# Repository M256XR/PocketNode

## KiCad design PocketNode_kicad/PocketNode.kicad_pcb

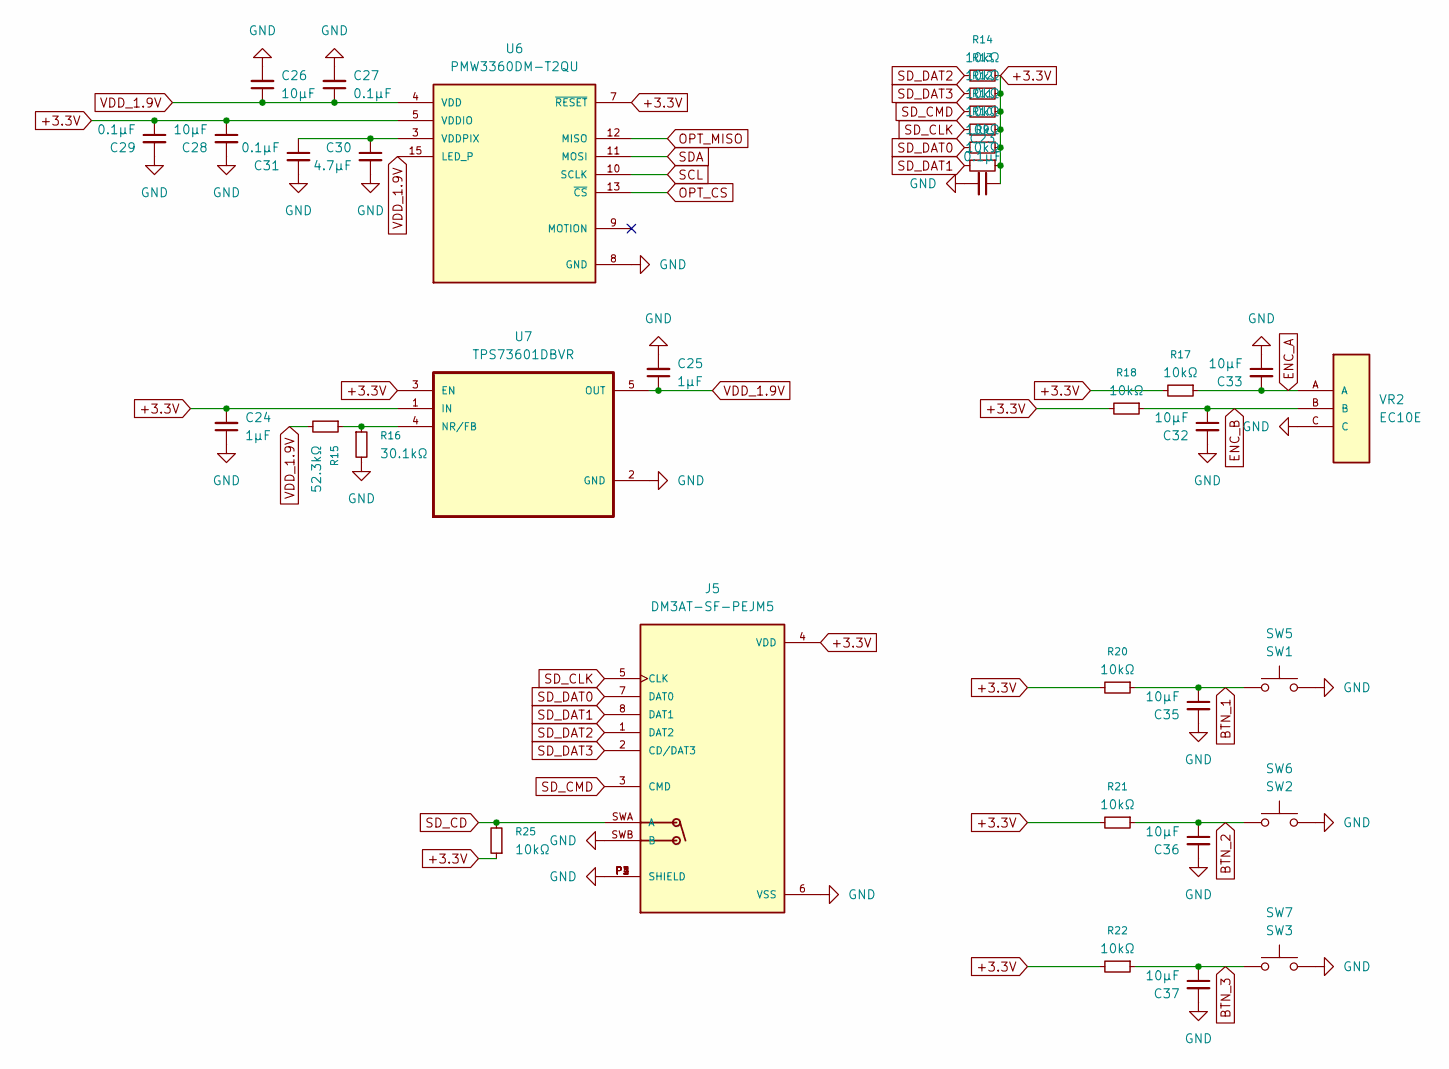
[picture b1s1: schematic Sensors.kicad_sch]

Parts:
C23, C27, C29, C31: 0.1μF; C_0603_1608Metric_Pad1.08x0.95mm_HandSolder
C24, C25: 1μF; C_0603_1608Metric_Pad1.08x0.95mm_HandSolder
C26, C28, C32, C33, C35, C36, C37: 10μF; C_0603_1608Metric_Pad1.08x0.95mm_HandSolder
C30: 4.7μF; C_0603_1608Metric_Pad1.08x0.95mm_HandSolder
J5: DM3AT-SF-PEJM5; HRS_DM3AT-SF-PEJM5
R9, R10, R11, R12, R13, R14, R17, R18, R20, R21, R22, R25: 10kΩ; R_0603_1608Metric_Pad0.98x0.95mm_HandSolder
R15: 52.3kΩ; R_0603_1608Metric_Pad0.98x0.95mm_HandSolder
R16: 30.1kΩ; R_0603_1608Metric_Pad0.98x0.95mm_HandSolder
SW5: SW1; SW_PUSH_6mm
SW6: SW2; SW_PUSH_6mm
SW7: SW3; SW_PUSH_6mm
U6: PMW3360DM-T2QU; PMW3360
U7: TPS73601DBVR; SOT95P280X145-5N
VR2: EC10E; TRIM_EC10E1220501

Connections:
+3.3V: C23.1, C24.2, C28.1, C29.1, J5.4 (VDD), R9.1, R10.1, R11.1, R12.1, R13.1, R14.1, R17.2, R18.2, R20.2, R21.2, R22.2, R25.1, U6.5 (VDDIO), U6.7 (~RESET), U7.1 (IN), U7.3 (EN); also elsewhere on the board
BTN_1: C35.1, R20.1, SW5.1; also elsewhere on the board
BTN_2: C36.1, R21.1, SW6.1; also elsewhere on the board
BTN_3: C37.1, R22.1, SW7.1; also elsewhere on the board
ENC_A: C33.2, R17.1, VR2.A; also elsewhere on the board
ENC_B: C32.1, R18.1, VR2.B; also elsewhere on the board
GND: C23.2, C24.1, C25.2, C26.2, C27.2, C28.2, C29.2, C30.2, C31.2, C32.2, C33.1, C35.2, C36.2, C37.2, J5.6 (VSS), J5.P1 (SHIELD), J5.P2 (SHIELD), J5.P3 (SHIELD), J5.P4 (SHIELD), J5.SWB (B), R16.2, SW5.2, SW6.2, SW7.2, U6.8 (GND), U7.2 (GND), VR2.C; also elsewhere on the board
unnamed: C30.1, C31.1, U6.3 (VDDPIX)
unnamed: R15.1, R16.1, U7.4 (NR/FB)
OPT_CS: U6.13 (~CS); also elsewhere on the board
OPT_MISO: U6.12 (MISO); also elsewhere on the board
SCL: U6.10 (SCLK); also elsewhere on the board
SDA: U6.11 (MOSI); also elsewhere on the board
SD_CD: J5.SWA (A), R25.2; also elsewhere on the board
SD_CLK: J5.5 (CLK), R11.2; also elsewhere on the board
SD_CMD: J5.3 (CMD), R12.2; also elsewhere on the board
SD_DAT0: J5.7 (DAT0), R10.2; also elsewhere on the board
SD_DAT1: J5.8 (DAT1), R9.2; also elsewhere on the board
SD_DAT2: J5.1 (DAT2), R14.2; also elsewhere on the board
SD_DAT3: J5.2 (CD/DAT3), R13.2; also elsewhere on the board
VDD_1.9V: C25.1, C26.1, C27.1, R15.2, U6.4 (VDD), U6.15 (LED_P), U7.5 (OUT)

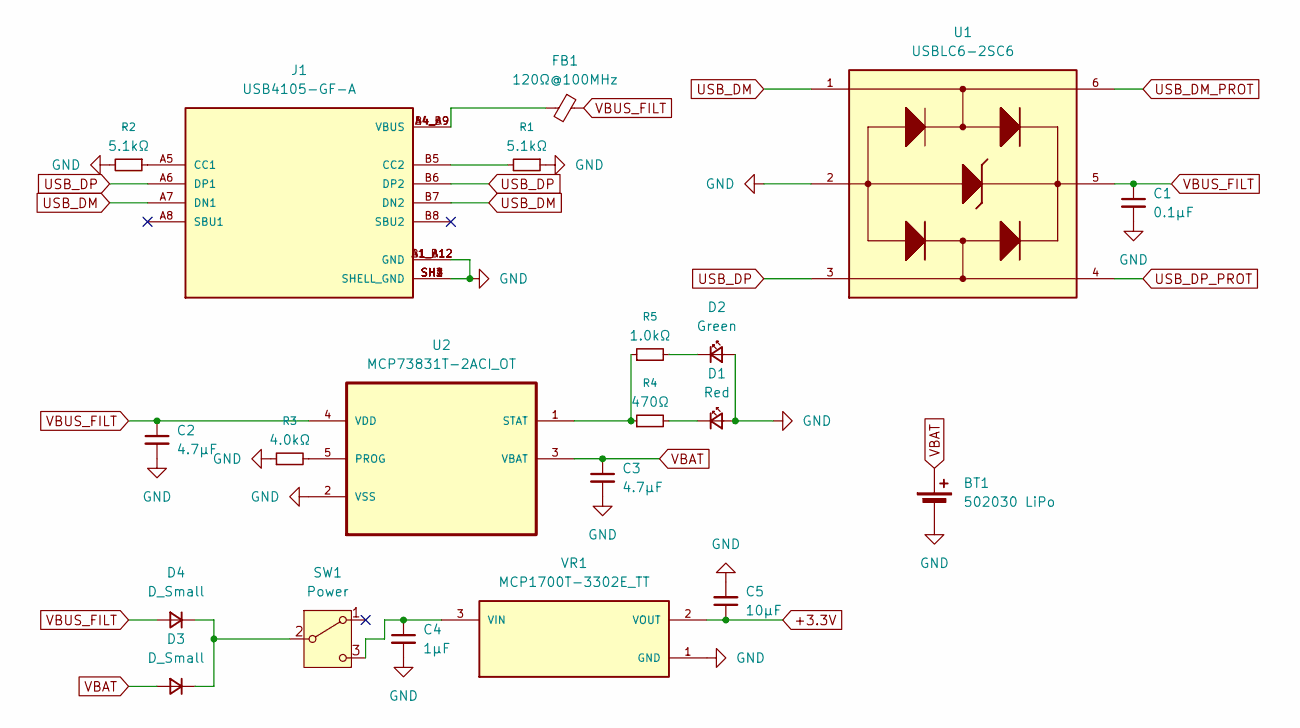
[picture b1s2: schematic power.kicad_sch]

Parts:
BT1: 502030 LiPo; PinHeader_1x02_P2.54mm_Vertical
C1: 0.1μF; C_0603_1608Metric_Pad1.08x0.95mm_HandSolder
C2, C3: 4.7μF; C_0603_1608Metric_Pad1.08x0.95mm_HandSolder
C4: 1μF; C_0603_1608Metric_Pad1.08x0.95mm_HandSolder
C5: 10μF; C_0603_1608Metric_Pad1.08x0.95mm_HandSolder
D1: Red; LED_0603_1608Metric_Pad1.05x0.95mm_HandSolder
D2: Green; LED_0603_1608Metric_Pad1.05x0.95mm_HandSolder
D3, D4: D_Small; D_0603_1608Metric_Pad1.05x0.95mm_HandSolder
FB1: 120Ω@100MHz; BEADC1608X95N
J1: USB4105-GF-A; GCT_USB4105-GF-A
R1, R2: 5.1kΩ; R_0603_1608Metric_Pad0.98x0.95mm_HandSolder
R3: 4.0kΩ; R_0603_1608Metric_Pad0.98x0.95mm_HandSolder
R4: 470Ω; R_0603_1608Metric_Pad0.98x0.95mm_HandSolder
R5: 1.0kΩ; R_0603_1608Metric_Pad0.98x0.95mm_HandSolder
SW1: Power; SW_Slide_SPDT_Angled_CK_OS102011MA1Q
U1: USBLC6-2SC6; SOT95P280X145-6N
U2: MCP73831T-2ACI_OT; SOT95P280X145-5N
VR1: MCP1700T-3302E_TT; SOT95P237X112-3N

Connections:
+3.3V: C5.1, VR1.2 (VOUT); also elsewhere on the board
GND: BT1.2 (-), C1.2, C2.2, C3.2, C4.2, C5.2, D1.2 (A), D2.2 (A), J1.A1_B12 (GND), J1.B1_A12 (GND), J1.SH1 (SHELL_GND), J1.SH2 (SHELL_GND), J1.SH3 (SHELL_GND), J1.SH4 (SHELL_GND), R1.1, R2.2, R3.1, U1.2, U2.2 (VSS), VR1.1 (GND); also elsewhere on the board
unnamed: D1.1 (K), R4.2
unnamed: D2.1 (K), R5.2
unnamed: D3.1 (K), D4.1 (K), SW1.2 (B)
unnamed: FB1.2, J1.A4_B9 (VBUS), J1.B4_A9 (VBUS)
unnamed: J1.A5 (CC1), R2.1
unnamed: J1.B5 (CC2), R1.2
unnamed: C4.1, SW1.3 (C), VR1.3 (VIN)
unnamed: R3.2, U2.5 (PROG)
unnamed: R4.1, R5.1, U2.1 (STAT)
USB_DM: J1.A7 (DN1), J1.B7 (DN2), U1.1
USB_DM_PROT: U1.6; also elsewhere on the board
USB_DP: J1.A6 (DP1), J1.B6 (DP2), U1.3
USB_DP_PROT: U1.4; also elsewhere on the board
VBAT: BT1.1 (+), C3.1, D3.2 (A), U2.3 (VBAT); also elsewhere on the board
VBUS_FILT: C1.1, C2.1, D4.2 (A), FB1.1, U1.5, U2.4 (VDD)

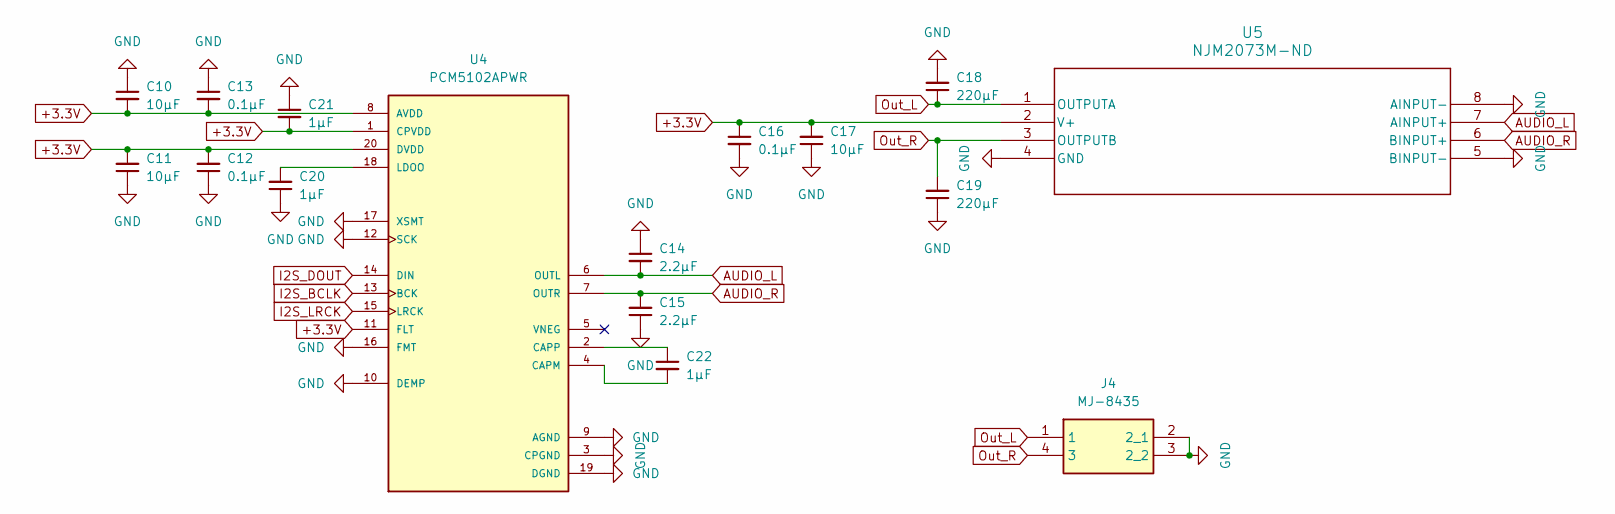
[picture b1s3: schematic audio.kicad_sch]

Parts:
C10, C11, C17: 10μF; C_0603_1608Metric_Pad1.08x0.95mm_HandSolder
C12, C13, C16: 0.1μF; C_0603_1608Metric_Pad1.08x0.95mm_HandSolder
C14, C15: 2.2μF; C_0603_1608Metric_Pad1.08x0.95mm_HandSolder
C18, C19: 220μF; C_0805_2012Metric_Pad1.18x1.45mm_HandSolder
C20, C21, C22: 1μF; C_0603_1608Metric_Pad1.08x0.95mm_HandSolder
J4: MJ-8435; Manufacturer_Part_Number MJ-8435
U4: PCM5102APWR; SOP65P640X120-20N
U5: NJM2073M-ND; NJR-DMP8_NJR

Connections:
+3.3V: C10.2, C11.2, C12.2, C13.2, C16.1, C17.2, C21.2, U4.1 (CPVDD), U4.8 (AVDD), U4.11 (FLT), U4.20 (DVDD), U5.2 (V+); also elsewhere on the board
AUDIO_L: C14.2, U4.6 (OUTL), U5.7 (AINPUT+)
AUDIO_R: C15.2, U4.7 (OUTR), U5.6 (BINPUT+)
GND: C10.1, C11.1, C12.1, C13.1, C14.1, C15.1, C16.2, C17.1, C18.2, C19.1, C20.1, C21.1, J4.2 (2_1), J4.3 (2_2), U4.3 (CPGND), U4.9 (AGND), U4.10 (DEMP), U4.12 (SCK), U4.16 (FMT), U4.17 (XSMT), U4.19 (DGND), U5.4 (GND), U5.5 (BINPUT-), U5.8 (AINPUT-); also elsewhere on the board
I2S_BCLK: U4.13 (BCK); also elsewhere on the board
I2S_DOUT: U4.14 (DIN); also elsewhere on the board
I2S_LRCK: U4.15 (LRCK); also elsewhere on the board
unnamed: C22.2, U4.4 (CAPM)
unnamed: C22.1, U4.2 (CAPP)
unnamed: C20.2, U4.18 (LDOO)
Out_L: C18.1, J4.1, U5.1 (OUTPUTA)
Out_R: C19.2, J4.4 (3), U5.3 (OUTPUTB)

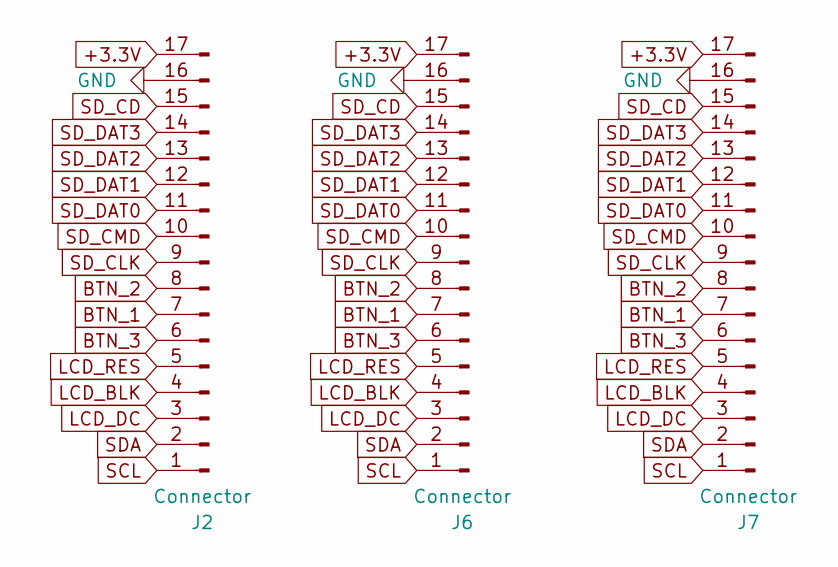
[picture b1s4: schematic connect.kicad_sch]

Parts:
J2, J6, J7: Connector; PinSocket_1x17_P2.00mm_Horizontal

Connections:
+3.3V: J2.17, J6.17, J7.17; also elsewhere on the board
BTN_1: J2.7, J6.7, J7.7; also elsewhere on the board
BTN_2: J2.8, J6.8, J7.8; also elsewhere on the board
BTN_3: J2.6, J6.6, J7.6; also elsewhere on the board
GND: J2.16, J6.16, J7.16; also elsewhere on the board
LCD_BLK: J2.4, J6.4, J7.4; also elsewhere on the board
LCD_DC: J2.3, J6.3, J7.3; also elsewhere on the board
LCD_RES: J2.5, J6.5, J7.5; also elsewhere on the board
SCL: J2.1, J6.1, J7.1; also elsewhere on the board
SDA: J2.2, J6.2, J7.2; also elsewhere on the board
SD_CD: J2.15, J6.15, J7.15; also elsewhere on the board
SD_CLK: J2.9, J6.9, J7.9; also elsewhere on the board
SD_CMD: J2.10, J6.10, J7.10; also elsewhere on the board
SD_DAT0: J2.11, J6.11, J7.11; also elsewhere on the board
SD_DAT1: J2.12, J6.12, J7.12; also elsewhere on the board
SD_DAT2: J2.13, J6.13, J7.13; also elsewhere on the board
SD_DAT3: J2.14, J6.14, J7.14; also elsewhere on the board

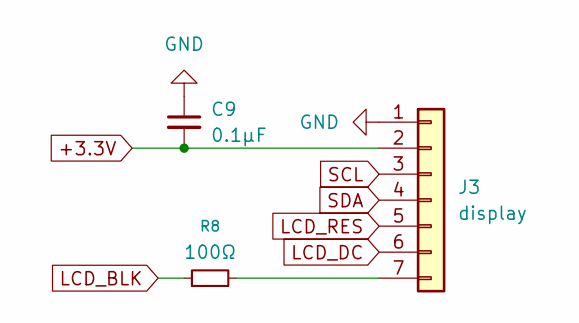
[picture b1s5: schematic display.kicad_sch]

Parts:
C9: 0.1μF; C_0603_1608Metric_Pad1.08x0.95mm_HandSolder
J3: display; PinSocket_1x07_P2.54mm_Vertical
R8: 100Ω; R_0603_1608Metric_Pad0.98x0.95mm_HandSolder

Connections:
+3.3V: C9.2, J3.2; also elsewhere on the board
GND: C9.1, J3.1; also elsewhere on the board
LCD_BLK: R8.1; also elsewhere on the board
LCD_DC: J3.6; also elsewhere on the board
LCD_RES: J3.5; also elsewhere on the board
unnamed: J3.7, R8.2
SCL: J3.3; also elsewhere on the board
SDA: J3.4; also elsewhere on the board

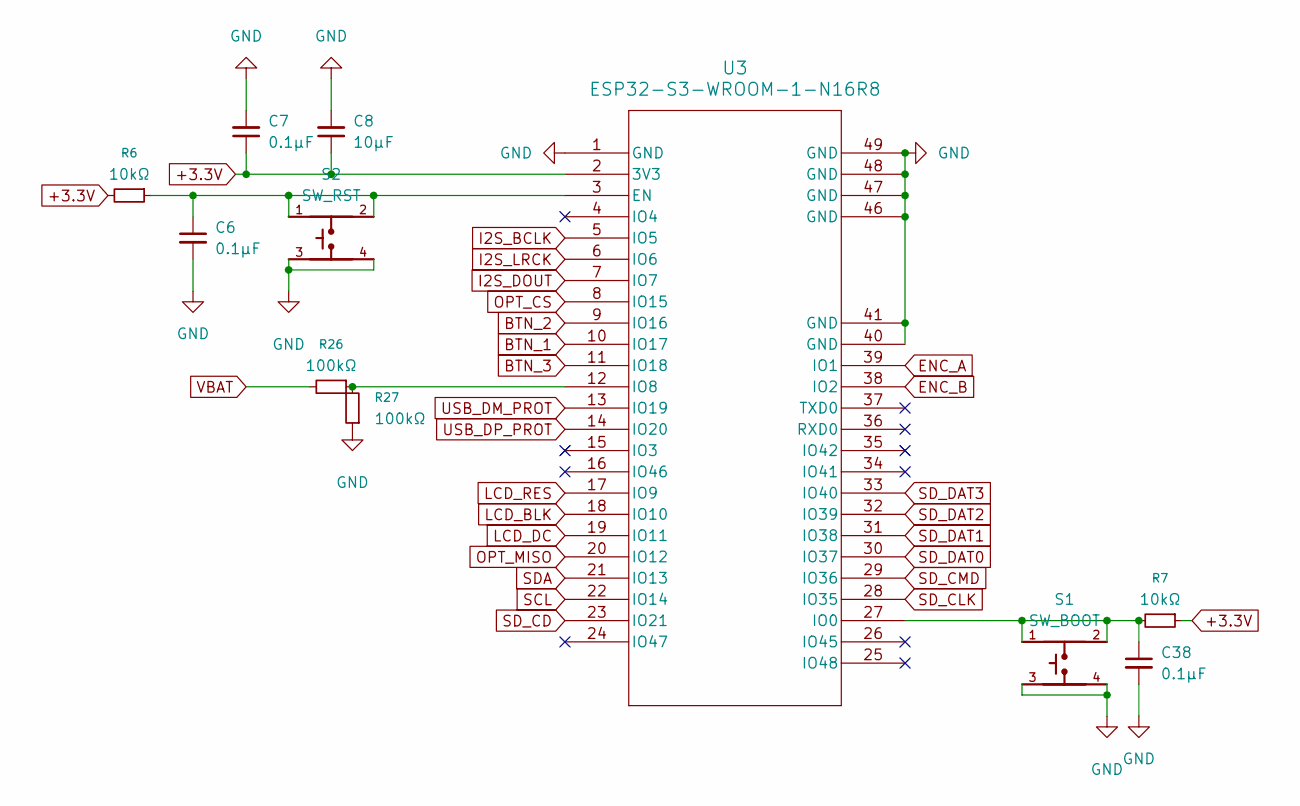
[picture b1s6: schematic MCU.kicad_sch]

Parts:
C6, C7, C38: 0.1μF; C_0603_1608Metric_Pad1.08x0.95mm_HandSolder
C8: 10μF; C_0603_1608Metric_Pad1.08x0.95mm_HandSolder
R6, R7: 10kΩ; R_0603_1608Metric_Pad0.98x0.95mm_HandSolder
R26, R27: 100kΩ; R_0603_1608Metric_Pad0.98x0.95mm_HandSolder
S1: SW_BOOT; SW_SKRPACE010
S2: SW_RST; SW_SKRPACE010
U3: ESP32-S3-WROOM-1-N16R8; ESP32-S3-WROOM-1_EXP

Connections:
+3.3V: C7.1, C8.1, R6.2, R7.1, U3.2 (3V3); also elsewhere on the board
BTN_1: U3.10 (IO17); also elsewhere on the board
BTN_2: U3.9 (IO16); also elsewhere on the board
BTN_3: U3.11 (IO18); also elsewhere on the board
ENC_A: U3.39 (IO1); also elsewhere on the board
ENC_B: U3.38 (IO2); also elsewhere on the board
GND: C6.2, C7.2, C8.2, C38.2, R27.1, S1.3, S1.4, S2.3, S2.4, U3.1 (GND), U3.40 (GND), U3.41 (GND), U3.46 (GND), U3.47 (GND), U3.48 (GND), U3.49 (GND); also elsewhere on the board
I2S_BCLK: U3.5 (IO5); also elsewhere on the board
I2S_DOUT: U3.7 (IO7); also elsewhere on the board
I2S_LRCK: U3.6 (IO6); also elsewhere on the board
LCD_BLK: U3.18 (IO10); also elsewhere on the board
LCD_DC: U3.19 (IO11); also elsewhere on the board
LCD_RES: U3.17 (IO9); also elsewhere on the board
unnamed: C6.1, R6.1, S2.1, S2.2, U3.3 (EN)
unnamed: C38.1, R7.2, S1.1, S1.2, U3.27 (IO0)
unnamed: R26.1, R27.2, U3.12 (IO8)
OPT_CS: U3.8 (IO15); also elsewhere on the board
OPT_MISO: U3.20 (IO12); also elsewhere on the board
SCL: U3.22 (IO14); also elsewhere on the board
SDA: U3.21 (IO13); also elsewhere on the board
SD_CD: U3.23 (IO21); also elsewhere on the board
SD_CLK: U3.28 (IO35); also elsewhere on the board
SD_CMD: U3.29 (IO36); also elsewhere on the board
SD_DAT0: U3.30 (IO37); also elsewhere on the board
SD_DAT1: U3.31 (IO38); also elsewhere on the board
SD_DAT2: U3.32 (IO39); also elsewhere on the board
SD_DAT3: U3.33 (IO40); also elsewhere on the board
USB_DM_PROT: U3.13 (IO19); also elsewhere on the board
USB_DP_PROT: U3.14 (IO20); also elsewhere on the board
VBAT: R26.2; also elsewhere on the board

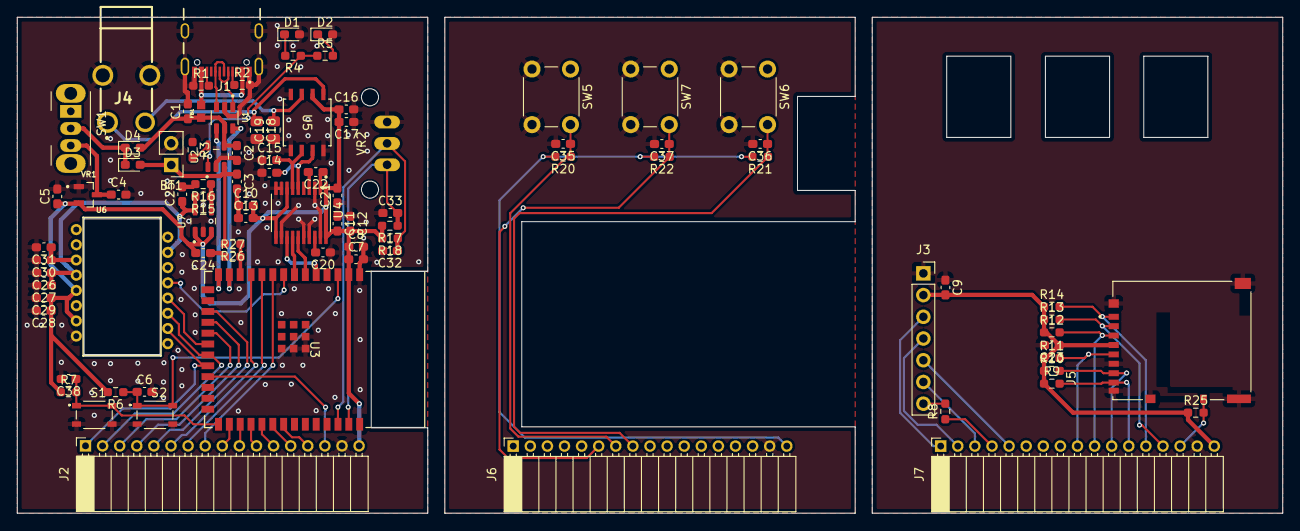
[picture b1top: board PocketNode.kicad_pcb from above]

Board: 2 copper layers, 148.0 x 58.0 mm, 89 parts (0 on the bottom side), 53 nets.

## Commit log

2025-10-20 first
2025-10-20 update2
2025-10-21 update3
2025-10-21 update4
2025-10-22 update5
2025-10-25 update11
